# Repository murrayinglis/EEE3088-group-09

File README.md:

# EEE3088-group-09
Electrical Engineering Design Process

Group members: 
-Murray Inglis INGMUR002
-Tinashe Timba TMBTIN004
-Ankush Chohan CHHANK001

Description:
The analogue sensor is a battery sensor that will record the voltage of the battery via communicating with the STM ADC.
The digital sensor is a light sensor chip that communicates using I2C with the STM.

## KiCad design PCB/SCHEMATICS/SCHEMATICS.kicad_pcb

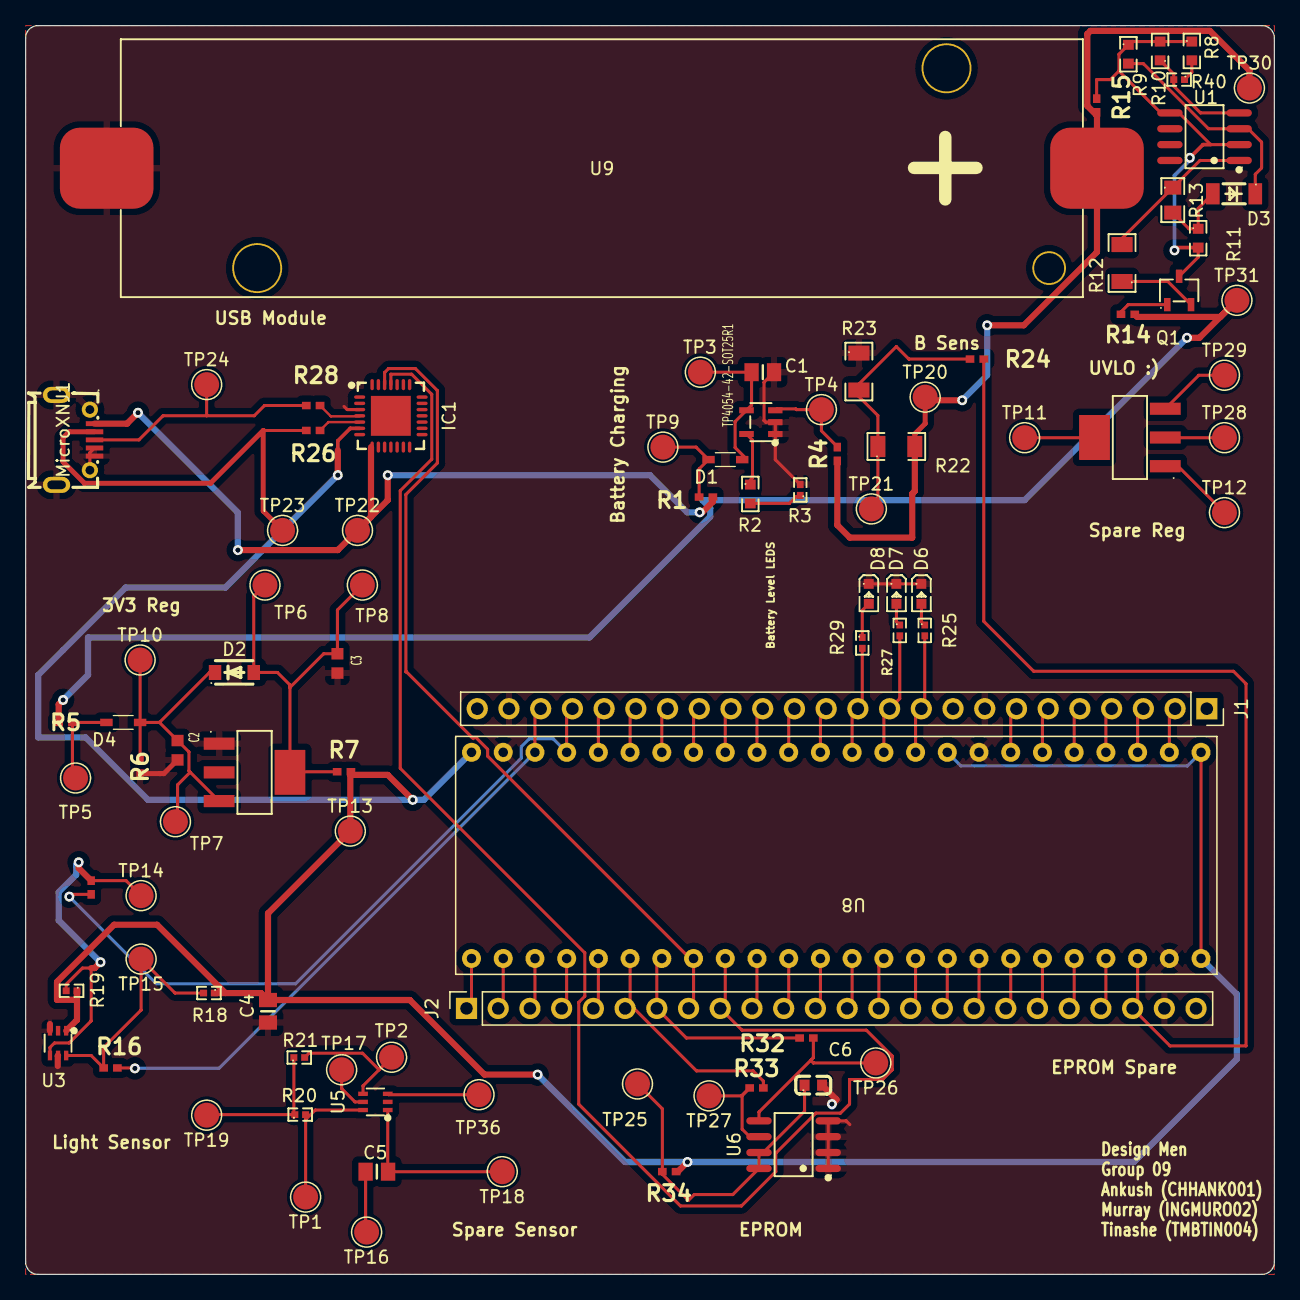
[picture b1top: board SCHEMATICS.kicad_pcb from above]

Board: 2 copper layers, 100.0 x 100.0 mm, 92 parts (0 on the bottom side), 86 nets.

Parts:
C1, C4, C5: 1uF; CAPC2012X140N
C2, C3: 10uF; CAPC1608X90N
C6: 3.3nF; C0603
D1, D4: D_Schottky; SOT323_INFINEON
D2: 1N4001; SOD-123F_L2.8-W1.8-LS3.7-RD
D3: D_Zener; LL-34_L3.5-W1.5-RD
D6, D7, D8: LED; LED0603-RD
IC1: CP2102-GMR; WQFN-28_L5.0-W5.0-P0.50-BL-EP3.2
J1, J2: Conn_01x24_Pin; PinSocket_1x24_P2.54mm_Vertical
MicroXNJ1: MICRO-USB-SMD_MICROXNJ
Q1: PMOS; SOT-23-3_L3.0-W1.6-P1.90-LS2.8-BR
R1, R4, R5, R7, R14, R15, R16, R17, R24, R26, R28, R32, R33, R34: 0; RESC1005X40N
R2: 150; R0603
R3: 1.5k; R0402
R6: 2.2k; RESC1005X40N
R8, R10: 3M; R0603
R9: 2.0M; R0603
R11: 150k; R0603
R12: 1M; R1206
R13: 10M; R0805
R18, R19, R20, R21, R25, R27, R29: 1k; R0402
R22, R23: 100k; R1206
R40: Value: Value: Value: Value: Value: Value: 510k; R0402
REF1, REF2: AMS1117-3_3_C369933; SOT-223-4_L6.5-W3.5-P2.30-LS7.0-BR
TP1, TP2, TP3, TP4, TP5, TP6, TP7, TP8, TP9, TP10, TP11, TP12, TP13, TP14, TP15, TP16, TP17, TP18, TP19, TP20, TP21, TP22, TP23, TP24, TP25, TP26, TP27, TP28, TP29, TP30, TP31, TP36: TestPoint; TestPoint_Pad_D2.0mm
TP4054-42-SOT25R1: SOT-23-5_L3.0-W1.7-P0.95-LS2.8-BL
U1: C7433; SOIC-8_L4.9-W3.9-P1.27-LS6.0-BL
U3, U5: LTR-303ALS-01; SOT-363_L2.0-W1.3-P0.65-LS2.1-BL
U6: C6482; SOIC-8_L4.9-W3.9-P1.27-LS6.0-BL
U8: STM32F051C6T6
U9: 18650_Holder_SMD

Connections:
/MICROCONTROLLER/5V: IC1.8 (VBUS), MicroXNJ1.1 (VBUS), R1.1, TP22.1
/MICROCONTROLLER/BOOT: J2.20, U8.44 (BOOT)
/MICROCONTROLLER/D+: IC1.4 (D+), R28.2
/MICROCONTROLLER/D-: IC1.5 (D-), R26.2
/MICROCONTROLLER/NRST: J1.7, U8.7 (NRST)
/MICROCONTROLLER/PA0: J1.10, R25.2, U8.10 (PA0)
/MICROCONTROLLER/PA1: J1.11, R27.2, U8.11 (PA1)
/MICROCONTROLLER/PA2: J1.12, R29.2, U8.12 (PA2)
/MICROCONTROLLER/PA3: J1.13, U8.13 (PA3)
/MICROCONTROLLER/PA4: J1.14, U8.14 (PA4)
/MICROCONTROLLER/PA5: J1.15, U8.15 (PA5)
/MICROCONTROLLER/PA6: J1.16, U8.16 (PA6)
/MICROCONTROLLER/PA7: J1.17, U8.17 (PA7)
/MICROCONTROLLER/PA8: J2.5, U8.29 (PA8)
/MICROCONTROLLER/PA9: J2.6, R33.2, U8.30 (PA9)
/MICROCONTROLLER/PA10: J2.7, R32.2, U8.31 (PA10)
/MICROCONTROLLER/PA11: IC1.26 (TXD), J2.8, U8.32 (PA11)
/MICROCONTROLLER/PA12: IC1.25 (RXD), J2.9, U8.33 (PA12)
/MICROCONTROLLER/PA13: J2.10, U8.34 (PA13)
/MICROCONTROLLER/PA14: J2.13, U8.37 (PA14)
/MICROCONTROLLER/PA15: J2.14, U8.38 (PA15)
/MICROCONTROLLER/PB0: J1.18, U8.18 (PB0)
/MICROCONTROLLER/PB1: J1.19, U8.19 (PB1)
/MICROCONTROLLER/PB2: J1.20, U8.20 (PB2)
/MICROCONTROLLER/PB3: J2.15, U8.39 (PB3)
/MICROCONTROLLER/PB4: J2.16, U8.40 (PB4)
/MICROCONTROLLER/PB5: J2.17, U8.41 (PB5)
/MICROCONTROLLER/PB6: J2.18, U8.42 (PB6)
/MICROCONTROLLER/PB7: J2.19, U8.43 (PB7)
/MICROCONTROLLER/PB8: J2.21, U8.45 (PB8)
/MICROCONTROLLER/PB9: J2.22, R24.2, U8.46 (PB9)
/MICROCONTROLLER/PB10: J1.21, R17.1, U8.21 (PB10)
/MICROCONTROLLER/PB11: J1.22, R16.1, U8.22 (PB11)
/MICROCONTROLLER/PB12: J2.1, U8.25 (PB12)
/MICROCONTROLLER/PB13: J2.2, U8.26 (PB13)
/MICROCONTROLLER/PB14: J2.3, U8.27 (PB14)
/MICROCONTROLLER/PB15: J2.4, U8.28 (PB15)
/MICROCONTROLLER/PC13: J1.2, U8.2 (PC13)
/MICROCONTROLLER/PC14: J1.3, U8.3 (PC14)
/MICROCONTROLLER/PC15: J1.4, U8.4 (PC15)
/MICROCONTROLLER/PF0: J1.5, U8.5 (PF0)
/MICROCONTROLLER/PF1: J1.6, U8.6 (PF1)
/MICROCONTROLLER/PF6: J2.11, U8.35 (PF6)
/MICROCONTROLLER/PF7: J2.12, U8.36 (PF7)
/MICROCONTROLLER/VSS: C4.2, IC1.6 (VDD), R7.2, R18.1, R19.1, R34.2, TP13.1, U3.1 (VDD), U8.1 (VBAT), U8.9 (V+), U8.24 (V+), U8.48 (V+)
/POWER MODULE/Battery: R4.2, R15.1, R22.2, TP20.1, TP30.1, U9.1 (+)
/POWER MODULE/UVLO Output: R5.1, R14.2, TP31.1
GND: C1.2, C2.2, C3.2, C4.1, C6.2, D6.1 (K), D7.1 (K), D8.1 (K), IC1.3 (GND), J1.8, J1.23, J2.23, MicroXNJ1.4 (ID), MicroXNJ1.5 (GND), MicroXNJ1.6 (SH1), MicroXNJ1.7 (SH2), MicroXNJ1.8 (SH3), MicroXNJ1.9 (SH4), R3.2, R6.2, R23.1, REF1.1 (GND/ADJ), TP4054-42-SOT25R1.1 (~CHRG), TP4054-42-SOT25R1.2 (GND), U3.3 (GND), U3.5 (INT), U6.1 (A0), U6.2 (A1), U6.3 (A2), U6.4 (GND), U8.8 (GND), U8.23 (GND), U8.47 (GND), U9.2 (-)
unnamed: C2.1, D2.1 (K), D4.C (K), R6.1, REF1.3 (Input), TP7.1, TP10.1
unnamed: Q1.3 (S), R8.1, R9.1, R10.2, R11.2, R15.2, U1.2 (V-), U1.5 (V+)
unnamed: C5.1, TP16.1
unnamed: C1.1, D1.C (K), TP3.1, TP4054-42-SOT25R1.4 (VCC)
unnamed: D1.A, R1.2, TP9.1
unnamed: C3.1, D2.2 (A), R7.1, REF1.4 (Output), TP6.1, TP8.1
unnamed: D3.2 (A), R11.1, R13.2
unnamed: D3.1 (K), R9.2, U1.3 (+)
unnamed: D4.A, R5.2, TP5.1
unnamed: D6.2 (A), R25.1
unnamed: D7.2 (A), R27.1
unnamed: D8.2 (A), R29.1
unnamed: MicroXNJ1.3 (D+), R28.1, TP24.1
unnamed: MicroXNJ1.2 (D-), R26.1, TP23.1
unnamed: Q1.1 (D), R14.1
unnamed: Q1.2 (G), R12.1
unnamed: R2.2, R3.1
unnamed: R12.2, R13.1, U1.1
unnamed: R20.1, R21.1, TP19.1
unnamed: R22.1, R23.2, R24.1, TP21.1
unnamed: R8.2, R40.1
unnamed: REF2.1 (GND/ADJ), TP12.1
unnamed: REF2.3 (Input), TP29.1
unnamed: REF2.2 (Output), TP28.1
unnamed: REF2.4 (Output), TP11.1
unnamed: R4.1, TP4.1, TP4054-42-SOT25R1.3 (BAT)
unnamed: R2.1, TP4054-42-SOT25R1.5 (PROG)
unnamed: R10.1, R40.2, U1.4 (-)
unnamed: R17.2, R19.2, TP14.1, U3.4 (SCL)
unnamed: R16.2, R18.2, TP15.1, U3.6 (SDA)
unnamed: TP36.1, U5.3 (GND)
unnamed: TP17.1, U5.5 (INT)
unnamed: R21.2, TP2.1, U5.4 (SCL)
unnamed: R20.2, TP1.1, U5.6 (SDA)
unnamed: C5.2, TP18.1, U5.1 (VDD)
unnamed: R33.1, TP27.1, U6.6 (SCL)
unnamed: R32.1, TP26.1, U6.5 (SDA)
unnamed: C6.1, R34.1, U6.7 (WP), U6.8 (VCC)

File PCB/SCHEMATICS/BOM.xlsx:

Reference | Value | Extended | LCSC | Unit price | Qty | Total
C1, C4, C5 | 1uF |  | C28323 | 5.7999999999999996E-3 | 3 | 1.7399999999999999E-2
C2, C3 | 10uF |  | C19702 | 6.6E-3 | 2 | 1.32E-2
C6 | 3.3nF |  | C1613 | 5.7999999999999996E-3 | 1 | 5.7999999999999996E-3
D1, D4, D5 | D_Schottky |  | C191023 | 1.67E-2 | 3 | 5.0099999999999999E-2
D2 | 1N4001 |  | C64898 | 7.1000000000000004E-3 | 1 | 7.1000000000000004E-3
D3 | D_Zener |  | C8056 | 1.11E-2 | 1 | 1.11E-2
D6-D8 | LED |  | C2286 | 5.4000000000000003E-3 | 3 | 1.6199999999999999E-2
IC1 | CP2102-GMR |  | C6568 | 2.3774000000000002 | 1 | 2.3774000000000002
MicroXNJ1 |  | YES | C404969 | 3.3300000000000003E-2 | 1 | 3.3300000000000003E-2
Q1 | PMOS | YES | C2959854 | 8.5099999999999995E-2 | 1 | 8.5099999999999995E-2
R1, R4, R5, R7, R14-R17, R24, R26, R28-R34 | 0 |  | C17168 | 5.0000000000000001E-4 | 17 | 8.5000000000000006E-3
R2 | 150 |  | C22808 | 1E-3 | 1 | 1E-3
R3 | 1.5k |  | C25867 | 5.0000000000000001E-4 | 1 | 5.0000000000000001E-4
R6, R25, R27 | 2.2k |  | C17520 | 1.6999999999999999E-3 | 3 | 5.0999999999999995E-3
R8, R10 | 3M |  | C23156 | 1.2999999999999999E-3 | 2 | 2.5999999999999999E-3
R9 | 2.0M |  | C22976 | 1.6000000000000001E-3 | 1 | 1.6000000000000001E-3
R11 | 150k |  | C22807 | 1E-3 | 1 | 1E-3
R12 | 1M |  | C17927 | 3.0999999999999999E-3 | 1 | 3.0999999999999999E-3
R13 | 10M |  | C26108 | 2.3999999999999998E-3 | 1 | 2.3999999999999998E-3
R18-R21 | 1k |  | C11702 | 5.0000000000000001E-4 | 4 | 2E-3
R22, R23 | 100k |  | C17900 | 3.0000000000000001E-3 | 2 | 6.0000000000000001E-3
R40 | 510k |  | C11616 | 5.0000000000000001E-4 | 1 | 5.0000000000000001E-4
REF1, REF2 | AMS1117-3_3_C369933 | YES | C369933 | 6.4600000000000005E-2 | 2 | 0.12920000000000001
TP4054-42-SOT25R1 |  |  | C32574 | 0.14330000000000001 | 1 | 0.14330000000000001
U1 | C7433 |  | C7433 | 0.28039999999999998 | 1 | 0.28039999999999998
U3, U5 | LTR-303ALS-01 | YES | C364577 | 0.38869999999999999 | 2 | 0.77739999999999998
U6, U7 | EPROM | YES | C6482 | 0.49059999999999998 | 2 | 0.98119999999999996
TOTAL |  |  |  |  |  | 4.9625000000000004

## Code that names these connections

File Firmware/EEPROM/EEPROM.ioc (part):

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Mcu.Name=STM32F051R8Tx
Mcu.Package=LQFP64
Mcu.UserName=STM32F051R8Tx
PA2.Mode=Asynchronous
PA2.Signal=USART2_TX
PA3.Mode=Asynchronous
PA3.Signal=USART2_RX
PB6.Mode=I2C
PB6.Signal=I2C1_SCL
PB7.Mode=I2C
PB7.Signal=I2C1_SDA
PC8.Signal=GPIO_Output
board=custom

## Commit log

2023-02-24 Added proposal template
2023-02-24 Test commit
2023-02-24 I am Ankush
2023-02-24 Added proposal document
2023-02-24 Populating proposal document
2023-02-26 Added Proposal.pdf
2023-02-26 Updated repo using template
2023-02-26 Updating to look like template
2023-03-04 uploaded initial designs
2023-03-05 Formatting folder
2023-03-05 Updated Schematics
2023-03-05 Added DEBUGGER
2023-03-05 UPDATED SCHEMATICS.
2023-03-05 Updated sym lib
2023-03-05 Added BOM
2023-03-05 Added Week 3 documents
2023-03-10 Updating schematics
2023-03-10 Name changes
2023-03-11 Adjusted Schematics
2023-03-12 Updated BOM
2023-03-12 Updated BOM CSV
2023-03-12 Updated Micro schematic
2023-03-12 BOM updated
2023-03-13 Finalizing week 4 document
2023-03-13 Updating EEPROM part no
2023-03-13 Adding bom to document
2023-03-17 Importing footprints for microcontroller
2023-03-18 Updating symbols and footprints
2023-03-19 Added footprints
2023-03-19 trying to merge
2023-03-19 Cleaning up
2023-03-19 UVLO simulation
2023-03-19 updated schematics and footprints
2023-03-19 Added sim lib table
2023-03-19 Added uct library
2023-03-19 Added stm
2023-03-19 Added battery
2023-03-19 Fixed ercs
2023-03-19 Fixing ERCs
2023-03-19 Added pwr flags
2023-03-19 Started PCB design
2023-03-20 updated path for footprints
2023-03-20 Fixed warning in PCB editor
2023-03-20 Creating ratsnest
2023-03-20 RATS NEST START
2023-03-20 Added traces
2023-03-20 Updating PCB
2023-03-20 Added parallel headers and edge cuts
2023-03-20 updated traces
2023-03-20 Updated pcb
2023-03-21 Made changes
2023-03-21 Updating document
2023-03-21 Labeled modules
2023-03-21 editing document
2023-03-21 added gerbers and BOM
2023-03-21 updates week doc
2023-03-24 added the peer review doc
2023-03-28 Uploaded pdf version
2023-03-28 final
2023-04-04 Added final docs
2023-04-13 Justins reccomendations
2023-04-13 Bom update
2023-04-23 Added report
2023-04-24 Updating week 9 doc
2023-04-24 added some totals and fixed some grammar issure in report
2023-04-24 Added PDF REPORT
2023-05-14 Week 13 assignment
